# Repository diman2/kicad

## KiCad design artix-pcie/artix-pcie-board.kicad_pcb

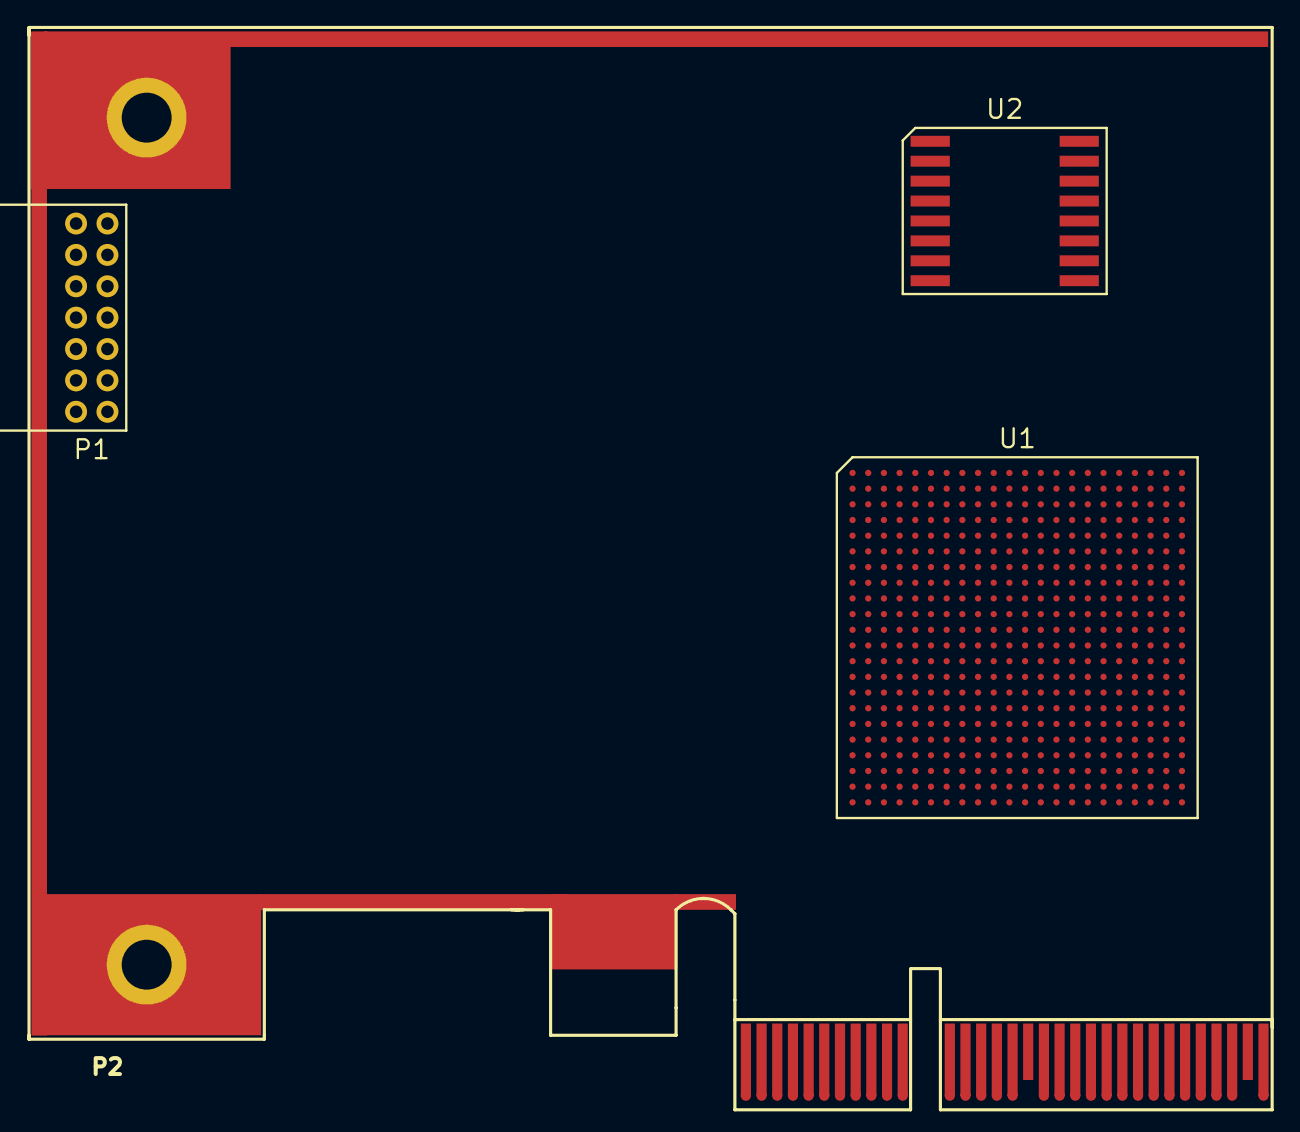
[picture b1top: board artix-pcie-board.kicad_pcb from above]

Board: 2 copper layers, 4 parts (0 on the bottom side), 16 nets, no tracks yet.

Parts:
P1: JTAG_CONN; JTAG_RA
P2: TOFE-4X; TOFE_4X_HalfHeight
U1: xc7a15tfgg484; Xil_Artix_BGA_484
U2: N25Q256_QSPI; micron_SOP2-16

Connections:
/Sheet5685901B/12V: P2.A2, P2.A3, P2.B1, P2.B2, P2.B3
/Sheet5685901B/GND: P2.A4, P2.A12, P2.A15, P2.A18, P2.A20, P2.A23, P2.A24, P2.A27, P2.A28, P2.A31, P2.B4, P2.B7, P2.B13, P2.B16, P2.B18, P2.B21, P2.B22, P2.B25, P2.B26, P2.B29, P2.B32
unnamed: U1.A2, U1.A3, U1.A5, U1.A7, U1.A9, U1.A11, U1.A12, U1.A22, U1.AA2, U1.AA12, U1.AA22, U1.AB9, U1.AB19, U1.B3, U1.B12, U1.B19, U1.C3, U1.C6, U1.C10, U1.C12, U1.C16, U1.D3, U1.D4, U1.D8, U1.D12, U1.D13, U1.E4, U1.E5, U1.E7, U1.E9, U1.E11, U1.E20, U1.F5, U1.F11, U1.F17, U1.G5, U1.G6, U1.G7, U1.G8, U1.G9, U1.G10, U1.G12, U1.G14, U1.H1, U1.H7, U1.H9, U1.H11, U1.H21, U1.J8, U1.J10, U1.J12, U1.J18, U1.K5, U1.K7, U1.K11, U1.K15, U1.L2, U1.L8, U1.L22, U1.M7, U1.M11, U1.M19, U1.N6, U1.N8, U1.N16, U1.P3, U1.P7, U1.P9, U1.P11, U1.P13, U1.R8, U1.R10, U1.R12, U1.R20, U1.T7, U1.T9, U1.T11, U1.T17, U1.U4, U1.U14, U1.V1, U1.V11, U1.V21, U1.W8, U1.W18, U1.Y5, U1.Y15
unnamed: U1.A17, U1.B14, U1.C21, U1.D18, U1.E15, U1.F22
unnamed: U1.AA7, U1.AB4, U1.R5, U1.T2, U1.V6, U1.W3
unnamed: U1.AA9, U1.AA10, U1.AA11, U1.AA13, U1.AA14, U1.AA15, U1.AA16, U1.AB10, U1.AB11, U1.AB12, U1.AB13, U1.AB15, U1.AB16, U1.AB17, U1.T14, U1.T15, U1.T16, U1.U15, U1.U16, U1.V10, U1.V13, U1.V14, U1.V15, U1.W10, U1.W11, U1.W12, U1.W14, U1.W15, U1.W16, U1.Y11, U1.Y12, U1.Y13, U1.Y14, U1.Y16, U1.Y17
unnamed: U1.AA17, U1.AB14, U1.V16, U1.W13, U1.Y10
unnamed: U1.B5, U1.B7, U1.B9, U1.B11, U1.C4, U1.C8
unnamed: U1.C1, U1.F2, U1.H6, U1.J3, U1.M4, U1.N1
unnamed: U1.D6, U1.D10, U1.E8, U1.F7, U1.F9
unnamed: U1.F12, U1.T12
unnamed: U1.G19, U1.H16, U1.J13, U1.K20, U1.L17, U1.N21
unnamed: U1.H8, U1.H10, U1.J7, U1.J9, U1.K8, U1.L7, U1.M8, U1.N7, U1.P8, U1.P10, U1.R7, U1.R9, U1.T8, U1.T10
unnamed: U1.H12, U1.K12, U1.M12, U1.P12, U1.R11
unnamed: U1.J11, U1.L11, U1.N11
unnamed: U1.M14, U1.P18, U1.R15, U1.T22, U1.U19, U1.Y20

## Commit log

2015-12-12 adding some experiments
2015-12-12 test4 is routed
2015-12-12 test4 is routed with planes
2015-12-16 still playing. created bga_144
2015-12-17 playing with schematic symbol editor
2015-12-22 adding schematic pseudo-symbol for AD9361
2015-12-28 working with the AD9361 BGA fanout
2015-12-29 working on artix pcie board
2015-12-29 cleaning up some early tests
2015-12-30 added qspi flash. need jtag connector next
2015-12-30 added jtag connector. consider CSG325 17x17mm package
2015-12-30 some new footprints added
2015-12-31 working on 0.8mm BGA problem
2015-12-31 wiring PCIe
2015-12-31 working the hierarchy
2015-12-31 thinking about power supplies
2015-12-31 adding fpga design to produce pinout
2015-12-31 fpga synthesizes but issues with refclk
2016-01-03 pcie design now compiles. need to determine pins for QSPI.
2016-01-03 clean up
2016-01-03 the CSG325 footprint
2016-01-03 pcie pins are constrained
2016-01-06 fpga compiles and reports power. need to add pmod, oscillator and power supply
2016-01-07 fpga compiles xc7a35t through xc7a200t in 484 package. xc7a15 does not support pcie design
